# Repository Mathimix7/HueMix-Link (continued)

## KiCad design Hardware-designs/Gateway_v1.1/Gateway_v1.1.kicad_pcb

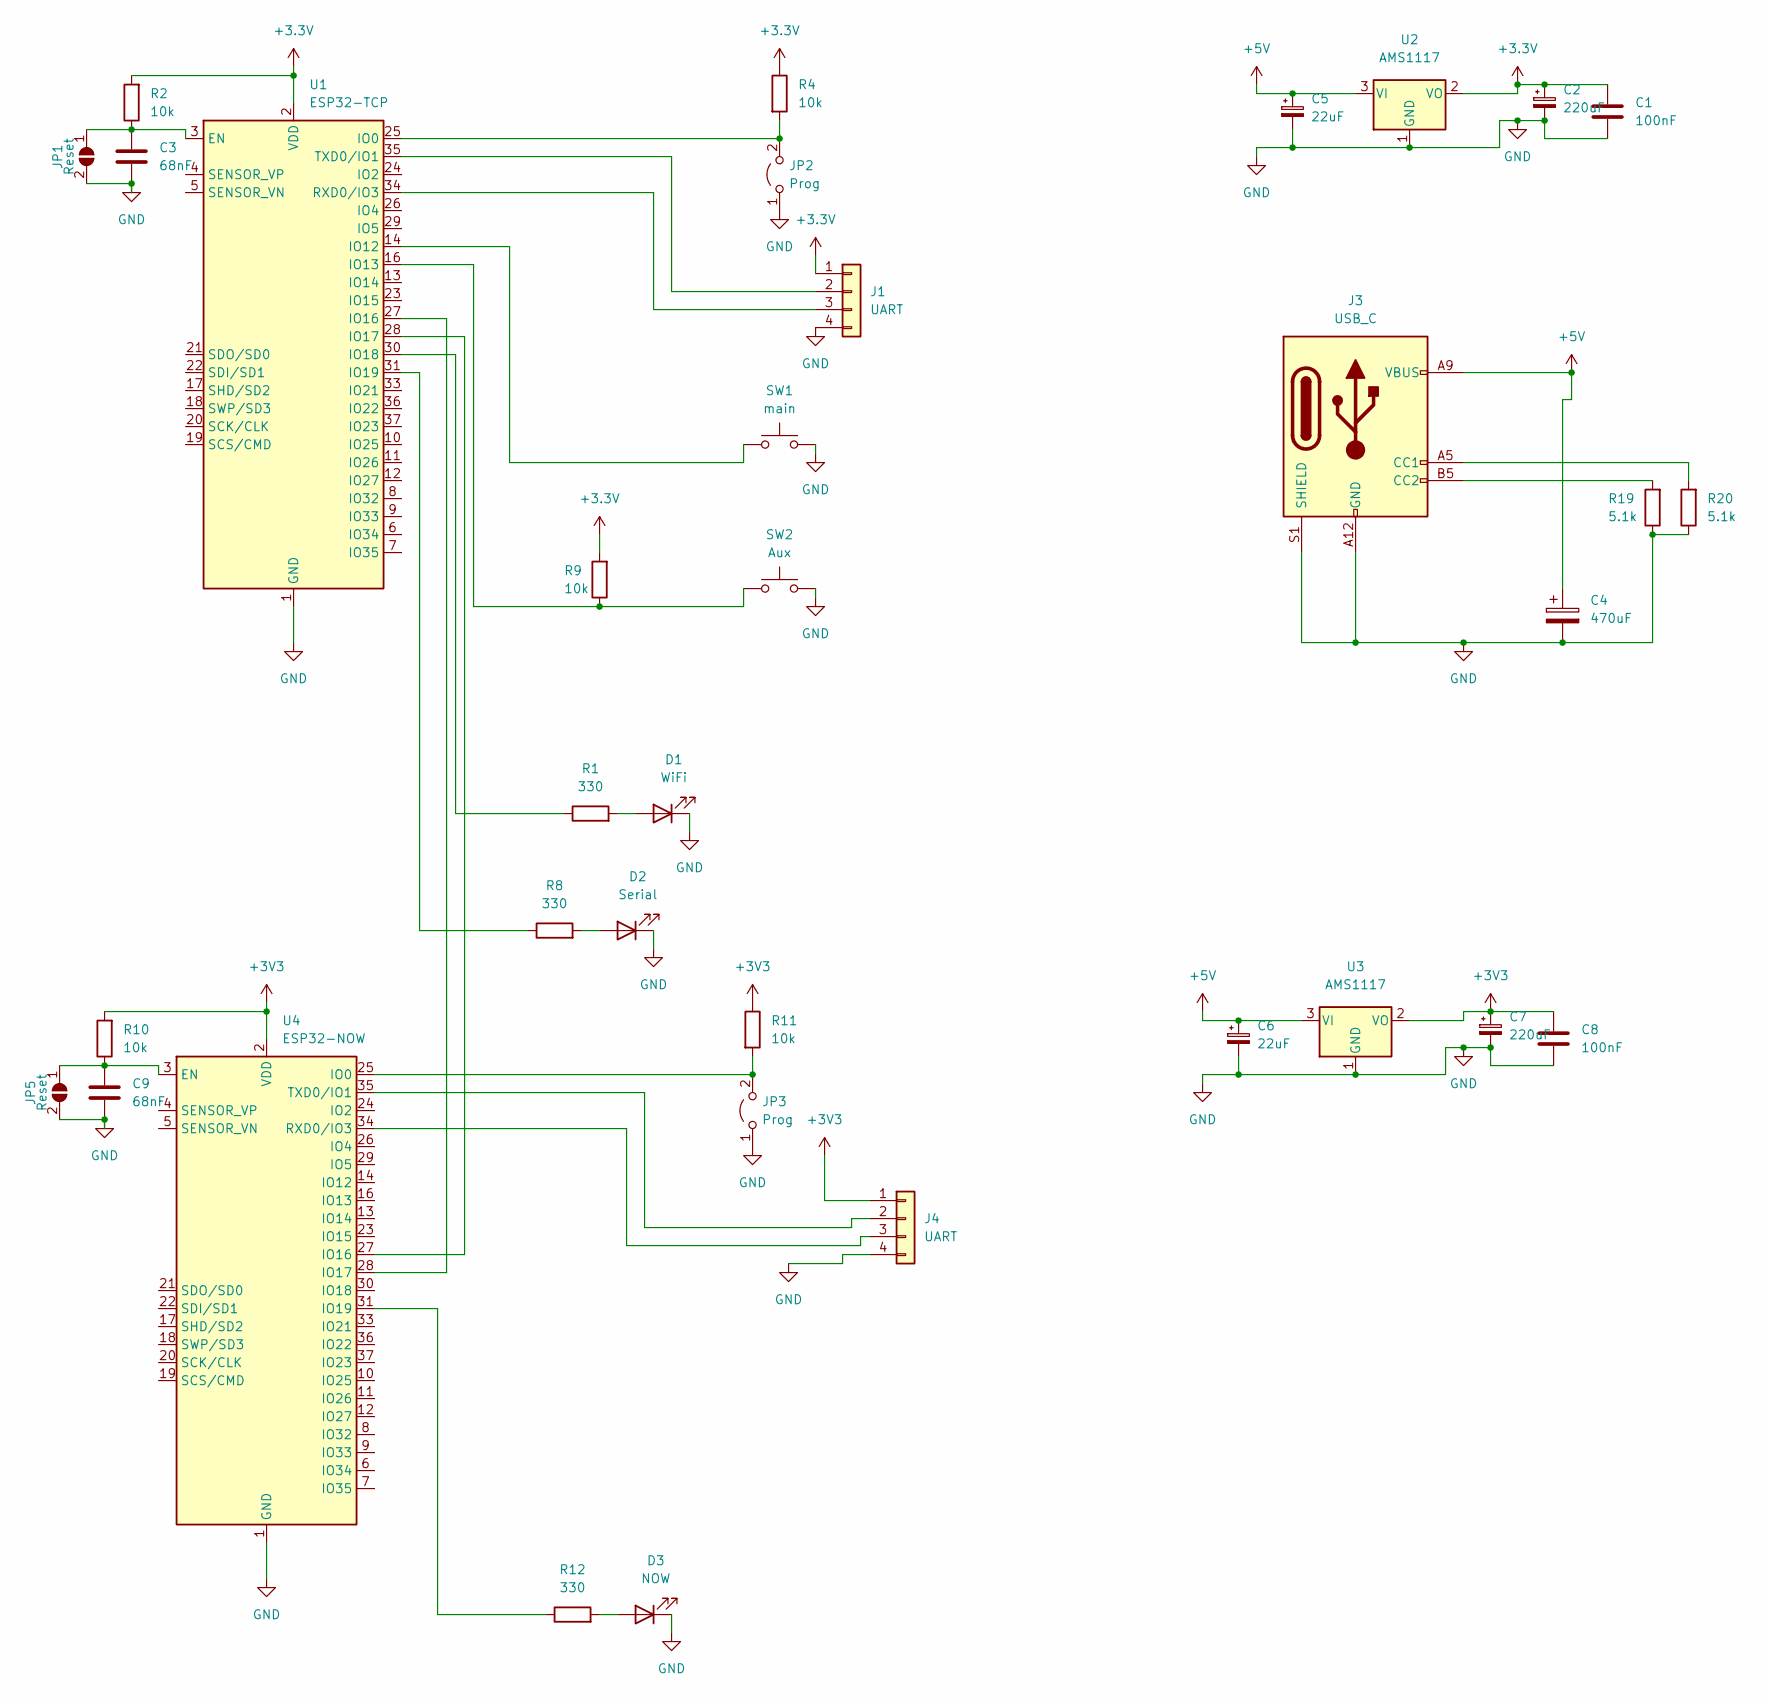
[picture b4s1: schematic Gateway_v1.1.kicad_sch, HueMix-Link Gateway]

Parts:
C1, C8: 100nF; C_0805_2012Metric_Pad1.18x1.45mm_HandSolder
C2, C7: 220uF; CP_EIA-6032-15_Kemet-U_HandSolder
C3, C9: 68nF; C_0805_2012Metric_Pad1.18x1.45mm_HandSolder
C4: 470uF; CP_Radial_D8.0mm_P3.50mm
C5, C6: 22uF; CP_EIA-6032-15_Kemet-U_HandSolder
D1: WiFi; LED_D3.0mm
D2: Serial; LED_D3.0mm
D3: NOW; LED_D3.0mm
J1, J4: UART; PinHeader_1x04_P2.54mm_Vertical
J3: USB_C; USB_C_Receptacle_GCT_USB4125-xx-x-0190_6P_TopMnt_Horizontal
JP1, JP5: Reset; SolderJumper-2_P1.3mm_Open_Pad1.0x1.5mm
JP2, JP3: Prog; PinHeader_1x02_P2.54mm_Vertical
R1, R8, R12: 330; R_1206_3216Metric_Pad1.30x1.75mm_HandSolder
R2, R4, R9, R10, R11: 10k; R_1206_3216Metric_Pad1.30x1.75mm_HandSolder
R19, R20: 5.1k; R_1206_3216Metric_Pad1.30x1.75mm_HandSolder
SW1: main; SW_PUSH-12mm
SW2: Aux; SW_PUSH_6mm
U1: ESP32-TCP; ESP32-WROOM-32
U2, U3: AMS1117; SOT-223-3_TabPin2
U4: ESP32-NOW; ESP32-WROOM-32

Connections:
+3.3V: C1.1, C2.1, J1.1, R2.2, R4.1, R9.2, U1.2 (VDD), U2.2 (VO)
+3V3: C7.1, C8.1, J4.1, R10.2, R11.1, U3.2 (VO), U4.2 (VDD)
+5V: C4.1, C5.1, C6.1, J3.A9 (VBUS), J3.B9 (VBUS), U2.3 (VI), U3.3 (VI)
GND: C1.2, C2.2, C3.2, C4.2, C5.2, C6.2, C7.2, C8.2, C9.2, D1.1 (K), D2.1 (K), D3.1 (K), J1.4, J3.A12 (GND), J3.B12 (GND), J3.S1 (SHIELD), J4.4, JP1.2 (B), JP2.1 (A), JP3.1 (A), JP5.2 (B), R19.1, R20.1, SW1.2, SW2.2, U1.1 (GND), U1.15 (GND), U1.38 (GND), U1.39 (GND), U2.1 (GND), U3.1 (GND), U4.1 (GND), U4.15 (GND), U4.38 (GND), U4.39 (GND)
unnamed: D1.2 (A), R1.2
unnamed: D2.2 (A), R8.2
unnamed: D3.2 (A), R12.2
unnamed: J1.2, U1.35 (TXD0/IO1)
unnamed: J1.3, U1.34 (RXD0/IO3)
unnamed: J3.A5 (CC1), R20.2
unnamed: J3.B5 (CC2), R19.2
unnamed: J4.2, U4.35 (TXD0/IO1)
unnamed: J4.3, U4.34 (RXD0/IO3)
unnamed: C3.1, JP1.1 (A), R2.1, U1.3 (EN)
unnamed: JP2.2 (B), R4.2, U1.25 (IO0)
unnamed: JP3.2 (B), R11.2, U4.25 (IO0)
unnamed: C9.1, JP5.1 (A), R10.1, U4.3 (EN)
unnamed: SW1.1, U1.14 (IO12)
unnamed: R9.1, SW2.1, U1.16 (IO13)
unnamed: U1.27 (IO16), U4.28 (IO17)
unnamed: U1.28 (IO17), U4.27 (IO16)
unnamed: R1.1, U1.30 (IO18)
unnamed: R8.1, U1.31 (IO19)
unnamed: R12.1, U4.31 (IO19)

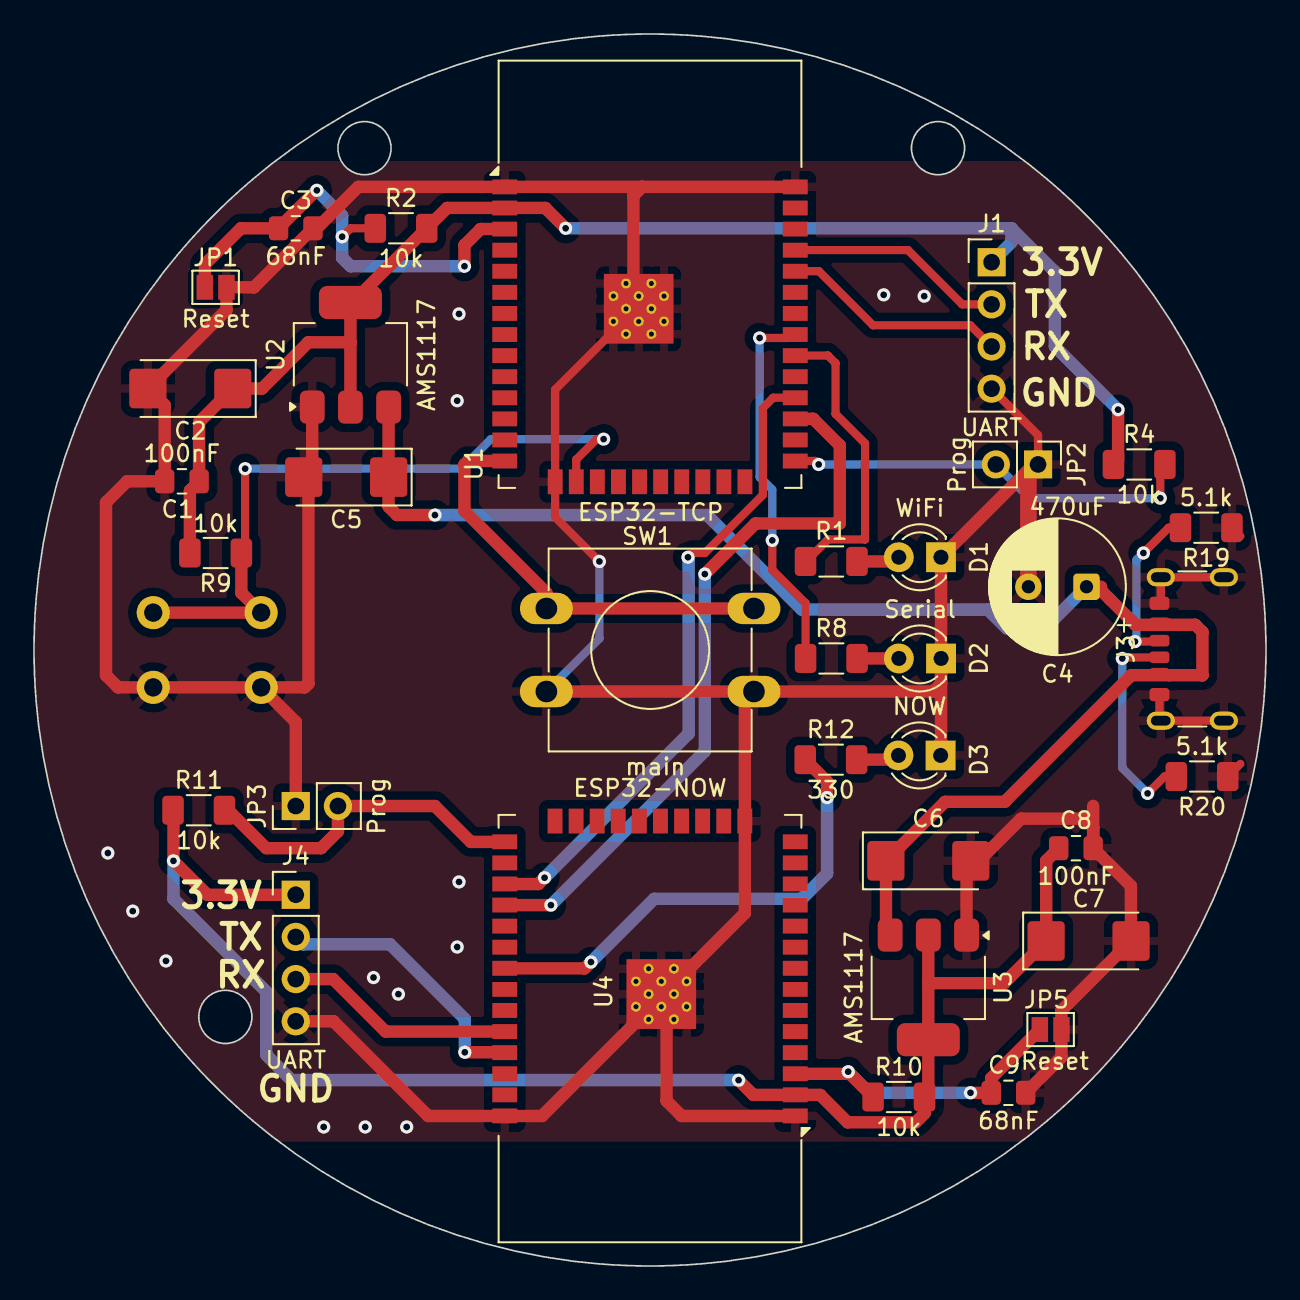
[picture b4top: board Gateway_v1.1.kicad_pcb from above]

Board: 2 copper layers, 74.2 x 74.2 mm, 35 parts (1 on the bottom side), 24 nets.

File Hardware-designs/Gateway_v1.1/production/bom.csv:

Designator,Footprint,Quantity,Value,LCSC Part #
"C1, C8",0805,2,100nF,
"C2, C7",CP_EIA-6032-15_Kemet-U_HandSolder,2,220uF,
"C3, C9",0805,2,1nF,
C4,CP_Radial_D8.0mm_P3.50mm,1,470uF,
"C5, C6",CP_EIA-6032-15_Kemet-U_HandSolder,2,22uF,
D1,LED_D3.0mm,1,WiFi,
D2,LED_D3.0mm,1,Serial,
D3,LED_D3.0mm,1,NOW,
"J1, J4",PinHeader_1x04_P2.54mm_Vertical,2,UART,
J3,USB_C_Receptacle_GCT_USB4125-xx-x-0190_6P_TopMnt_Horizontal,1,USB_C,
"JP1, JP5",SolderJumper-2_P1.3mm_Open_Pad1.0x1.5mm,2,Reset,
"JP2, JP3",PinHeader_1x02_P2.54mm_Vertical,2,Prog,
"R1, R12, R8",1206,3,330,
"R10, R11, R2, R4, R9",1206,5,10k,
"R19, R20",1206,2,5.1k,
SW1,SW_PUSH-12mm,1,main,
SW2,SW_PUSH_6mm,1,Aux,
U1,ESP32-WROOM-32,1,ESP32-TCP,
"U2, U3",SOT-223-3_TabPin2,2,AMS1117,
U4,ESP32-WROOM-32,1,ESP32-NOW,

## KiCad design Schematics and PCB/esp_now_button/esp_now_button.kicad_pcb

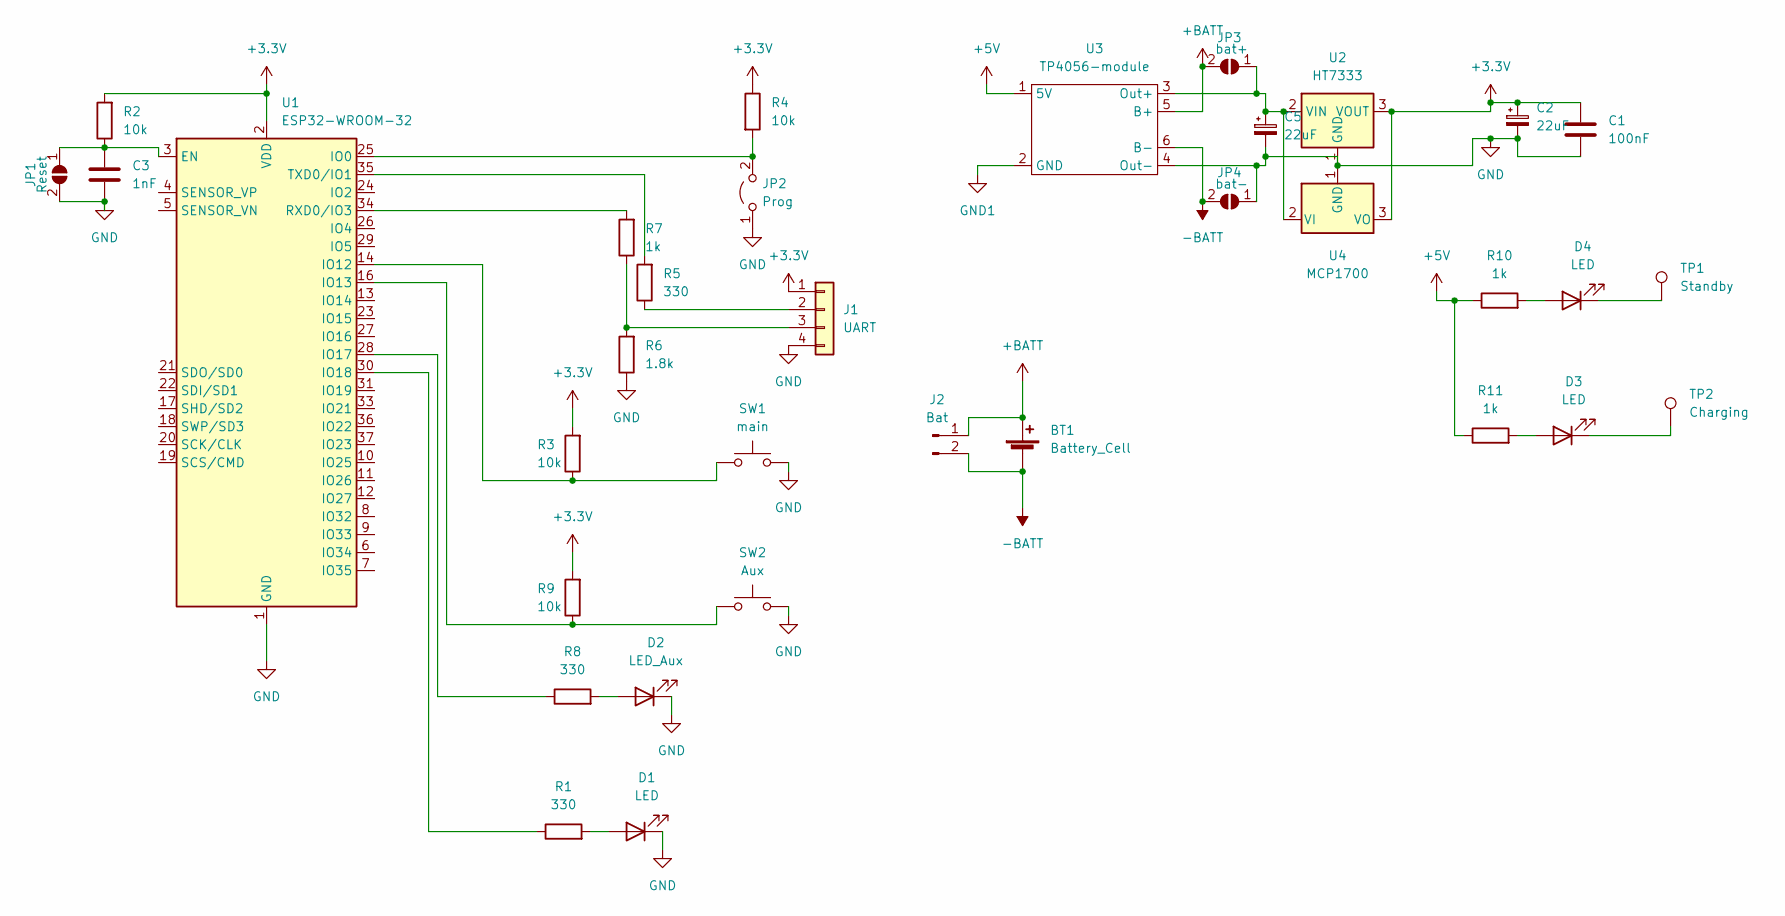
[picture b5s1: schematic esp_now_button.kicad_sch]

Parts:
BT1: Battery_Cell; BatteryHolder_ComfortableElectronic_CH273-2450_1x2450
C1: 100nF; C_0805_2012Metric_Pad1.18x1.45mm_HandSolder
C2, C5: 22uF; CP_EIA-6032-20_AVX-F_Pad2.25x2.35mm_HandSolder
C3: 1nF; C_0805_2012Metric_Pad1.18x1.45mm_HandSolder
D1, D3, D4: LED; LED_D3.0mm
D2: LED_Aux; LED_D3.0mm
J1: UART; PinHeader_1x04_P2.54mm_Vertical
J2: Bat; JST_EH_B2B-EH-A_1x02_P2.50mm_Vertical
JP1: Reset; SolderJumper-2_P1.3mm_Open_Pad1.0x1.5mm
JP2: Prog; PinHeader_1x02_P2.54mm_Vertical
JP3: bat+; SolderJumper-2_P1.3mm_Open_Pad1.0x1.5mm
JP4: bat-; SolderJumper-2_P1.3mm_Open_Pad1.0x1.5mm
R1, R5, R8: 330; R_1206_3216Metric_Pad1.30x1.75mm_HandSolder
R2, R3, R4, R9: 10k; R_1206_3216Metric_Pad1.30x1.75mm_HandSolder
R6: 1.8k; R_1206_3216Metric_Pad1.30x1.75mm_HandSolder
R7, R10, R11: 1k; R_1206_3216Metric_Pad1.30x1.75mm_HandSolder
SW1: main; SW_PUSH-12mm
SW2: Aux; SW_PUSH_6mm
TP1: Standby; TestPoint_THTPad_D1.5mm_Drill0.7mm
TP2: Charging; TestPoint_THTPad_D1.5mm_Drill0.7mm
U1: ESP32-WROOM-32
U2: HT7333; SOT-89-3
U3: TP4056-module; TP4056-18650
U4: MCP1700; TO-92_Inline

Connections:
+3.3V: C1.1, C2.1, J1.1, R2.2, R3.2, R4.1, R9.2, U1.2 (VDD), U2.3 (VOUT), U4.3 (VO)
+5V: R10.1, R11.1, U3.1 (5V)
+BATT: BT1.1 (+), J2.1, JP3.2 (B), U3.5 (B+)
-BATT: BT1.2 (-), J2.2, JP4.2 (B), U3.6 (B-)
GND: C1.2, C2.2, C3.2, C5.2, D1.1 (K), D2.1 (K), J1.4, JP1.2 (B), JP2.1 (A), JP4.1 (A), R6.1, SW1.2, SW2.2, U1.1 (GND), U1.15 (GND), U1.38 (GND), U1.39 (GND), U2.1 (GND), U3.4 (Out-), U4.1 (GND)
GND1: U3.2 (GND)
unnamed: C3.1, JP1.1 (A), R2.1, U1.3 (EN)
unnamed: C5.1, JP3.1 (A), U2.2 (VIN), U3.3 (Out+), U4.2 (VI)
unnamed: D1.2 (A), R1.2
unnamed: D2.2 (A), R8.2
unnamed: D3.1 (K), TP2.1
unnamed: D3.2 (A), R11.2
unnamed: D4.1 (K), TP1.1
unnamed: D4.2 (A), R10.2
unnamed: J1.2, R5.1
unnamed: J1.3, R6.2, R7.1
unnamed: JP2.2 (B), R4.2, U1.25 (IO0)
unnamed: R1.1, U1.30 (IO18)
unnamed: R3.1, SW1.1, U1.14 (IO12)
unnamed: R5.2, U1.35 (TXD0/IO1)
unnamed: R7.2, U1.34 (RXD0/IO3)
unnamed: R8.1, U1.28 (IO17)
unnamed: R9.1, SW2.1, U1.16 (IO13)

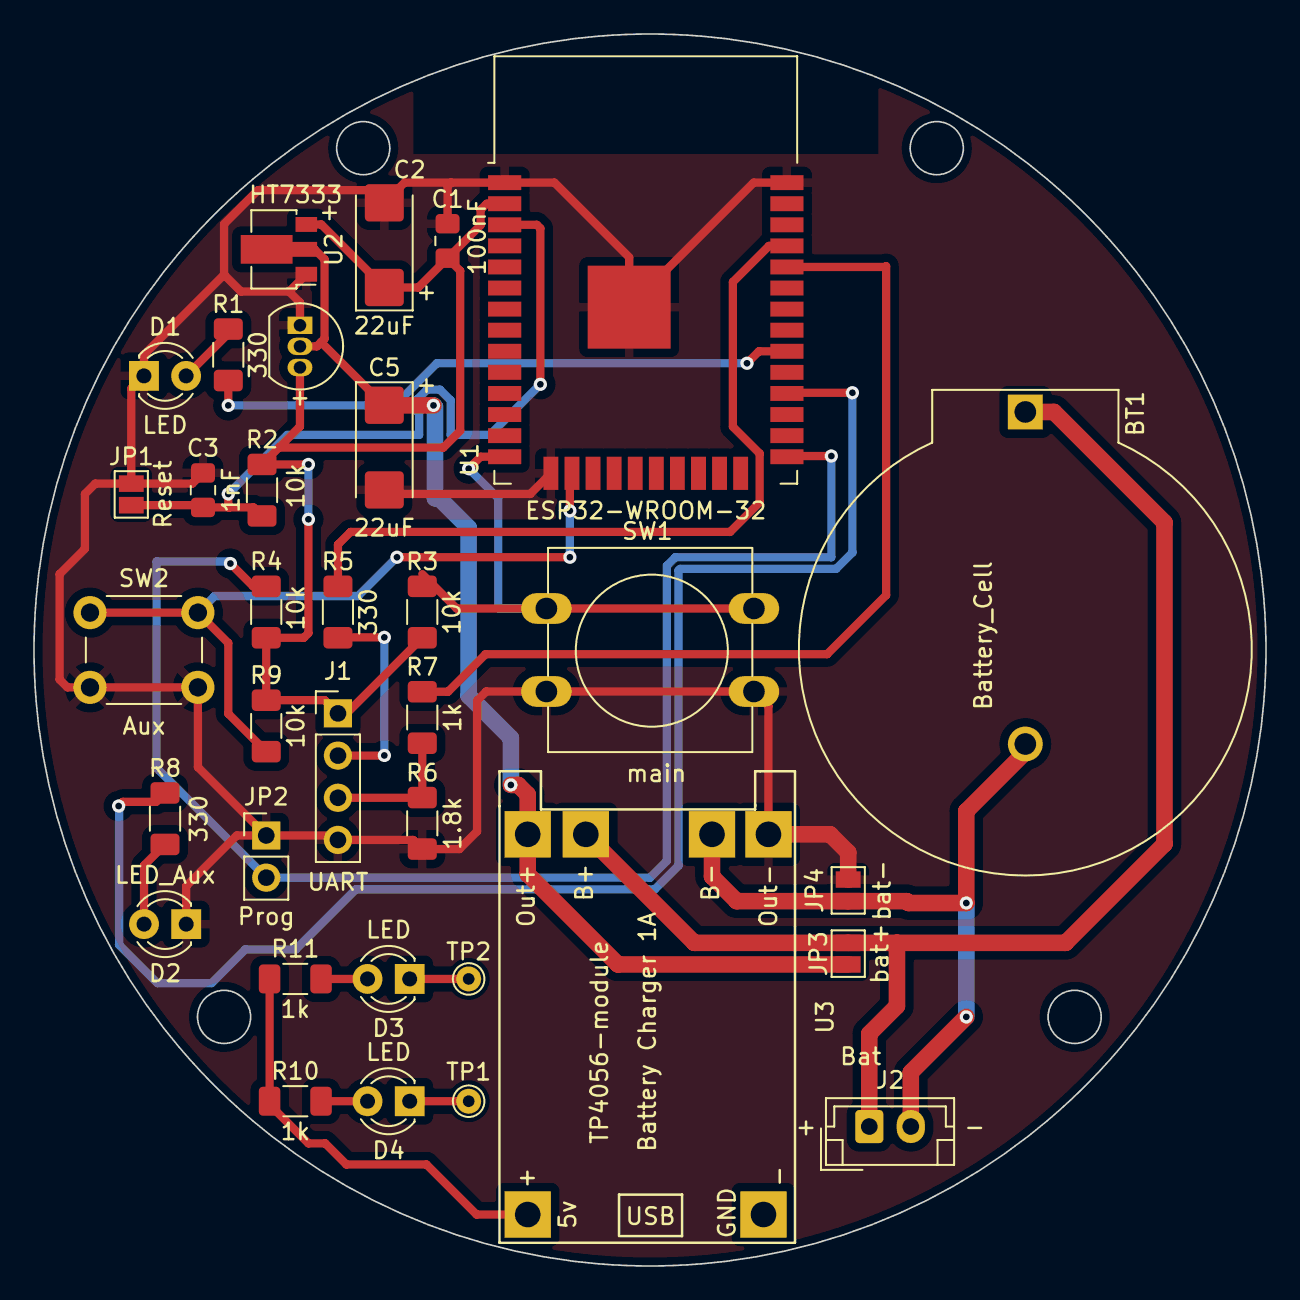
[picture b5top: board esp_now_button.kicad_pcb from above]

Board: 2 copper layers, 74.2 x 74.2 mm, 34 parts (0 on the bottom side), 22 nets.

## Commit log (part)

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2023-06-20 Moved Python files
2023-06-20 add arduino code
2023-06-20 add schematics and pcb
    Kicad files + gerbers
2023-06-20 Add PDF schematics
2023-06-20 add pcb images
2023-06-21 add services linux
2023-06-22 button version for esp8266
    It does not include deep sleep
2023-06-22 Erase data from files
2023-06-22 Update default port value
2023-06-23 Fix holding button and brightness
2023-06-26 Fix arduino files in folders
2023-06-26 tcp_client_server for esp8266
2023-06-26 update macAddress updater with button
2023-06-30 Change pins to pcb
2023-06-30 fix invalid servers macs + socket timeout
2023-06-30 change timeout to recieve
2023-07-01 fix holding sending wrong data
2023-07-01 update name
2023-07-03 update website main screen and buttons
    New color, responsive, better alerts, cancel buttons
2023-07-03 add ico
2023-07-03 changed servers and settings to new website style
2023-07-03 remove prints
2023-07-03 add new ico logo
2023-07-03 remove debug
2023-07-03 fix styles
2023-07-03 Fix enter action
    (Addition to website improvement pull request)
2023-07-08 add led off option
2023-07-09 new server information
    Server information, led off times, firmware update through website
2023-07-10 add loading screen and timeout for servers data
2023-07-10 fix erros loading
2023-07-10 fetch time from tcp instead of api
2023-07-10 bug fix
2023-07-10 Rename to setupRename.html
2023-09-02 duplicated files
2023-09-05 Create website blueprints
2023-09-05 Create API for buttons
2023-11-18 add server api support
2024-01-27 Create LICENSE
2025-12-07 Add .gitignore and update platformio.ini; refactor button handling in gateway_net_node and normal_button
2025-12-11 Refactor color handling and enhance light state management
    - Updated color conversion methods in ColorController to utilize model_id for gamut selection.
    - Added model_id to light state updates in HueStateManager.
    - Enhanced API responses to include model_id for lights.
    - Improved rooms overview data retrieval to use model_id for color conversions.
2025-12-12 WIP: local changes
2025-12-27 Final esp firmware version
2025-12-27 New network service, website endpoints, and configuration
2025-12-27 Final html version
2025-12-27 edit gitignore
2025-12-27 Fix backup reload, add notifiers, and file not existing management
2025-12-27 Add requirements.txt
2025-12-27 Add license and readme
2025-12-27 add waitress wsgi support
2025-12-27 Refactor logging levels to debug for specific events and add logging service for improved log management
2025-12-27 add logo
2025-12-27 Rename HueMix
2025-12-27 Add hostname option
2025-12-27 Update version
2025-12-27 Make installer output more readable with colored markers
2025-12-27 Enhance usage output with color-coded options for better readability
2025-12-27 Update usage output colors for improved visibility
2025-12-27 Update usage output colors for improved readability
2025-12-27 Remove symbols
2025-12-27 Fix hosts local installation
2025-12-27 Fix logging messages format for systemd
2025-12-27 Remove upload_port entries from platformio.ini for all environments
2025-12-27 WIP: Proxy setup
2025-12-27 Finish proxy for webserver and new domain management. Remove flask port setup
2025-12-27 Finish touches for install script.
2025-12-27 Make commands silent
2025-12-27 Fix service_update_finish
2025-12-27 Fix permission setup
2025-12-27 Fix local domain errors
2025-12-27 Use HAProxy
2025-12-27 fixe old hostname changes with avahi service file
2025-12-27 Fix hostname with .local
2025-12-27 Add automation engine system status
2025-12-27 Upgrade version
2025-12-28 Change led type
2025-12-28 Refactor LED control logic to use LED_ACTIVE_HIGH for consistency
2025-12-29 Add clear LED schedule functionality with confirmation modal
2025-12-29 Remove configured scene from button when original scene is deleted. And handle delete/add SSE events for lights, scenes, and rooms
2025-12-29 Fix: Replace print with logger
2025-12-29 Change devices ids to uuid4
2025-12-30 Fix lights brightness issue not restoring properly
2025-12-30 Remove print
2025-12-30 Fix issue with not configured buttons
2025-12-30 Improved all bridge overview information to update in real time and
2025-12-30 Flash button when pressed on settings page
2025-12-30 Version bump
2025-12-30 Made local flag opposite
2025-12-30 Add backup deletion
2025-12-30 Fix issue with service not being detected properly
2026-01-13 Add device type definitions and update packet payloads for gateway, light, and button. Fix button not activating with short presses
2026-01-13 feat: Add remote control support and configuration
    - Updated DeviceManager to handle remote devices with new device_type parameter.
    - Enhanced NetworkServer to process HELLO packets from remote controls and manage pairing.
    - Implemented PacketDecoder changes to recognize remote devices and their actions.
    - Modified PairingManager to include remote devices in allowed types.
    - Added API endpoints for configuring remote controls with per-button actions and room mappings.
    - Created a new modal in the frontend for remote configuration, allowing users to set actions and scenes for each button.
2026-01-13 Implementation of battery status
2026-01-13 bump
2026-01-13 Fix installer logs
2026-01-13 Add remote to pairing devices
2026-01-13 Fix direction toggle on remote
2026-01-13 Improve HAProxy restart command to suppress unnecessary output
2026-01-15 Fix resistor divider
2026-01-25 OTA update working for all devices
2026-01-26 Change signature protocol to always include full length, fix radio node not updating properly.
2026-01-27 Add build_release script, update platformio.ini, and enhance OTA functionality
2026-01-27 Add serial firmware upload
2026-01-28 Add scene cycle action for remote buttons and enhance device management UI
2026-01-31 Refactor color conversion methods and enhance network server reliability with socket checks
2026-01-31 Fix small ota issues
2026-02-01 Refactor OTA HTML to use local ESPTool bundle instead of unpkg
2026-02-01 version
2026-02-01 Bump version to 3.8.1; update DOUBLE_TAP_WINDOW to 1000ms in button firmware and improve remote button event handling
2026-02-12 Update pairing to https for bridge pro
2026-02-12 Update pairing to https fix
2026-02-13 Hardware Design
2026-02-14 Update color functions and add new lightstrip model
2026-02-16 Motion sensor initial commit
2026-02-17 Restore images
2026-02-17 Remove DS_Store
2026-02-17 Ignore KiCad backup/local files in Hardware-designs
2026-02-18 Add pcb images, step file, and pdf schematic for all hardware designs.
2026-02-18 Add production output for remote.
2026-02-18 Revert "Update color functions and add new lightstrip model"
    This reverts commit 1c41b5c88474862ff84bd28d54ce498e215f0f58.
2026-02-20 add motion sensor hardware
2026-02-21 Add serial labels on pcb
2026-02-22 feat: Configurable 1-4 button remotes with triple-tap configuration
    Add flexible button count (1-4) for ESP32 remotes configured via
    triple-tap reset + held button combinations. Includes hardware pattern
    validation, dynamic wakeup masks, custom UI naming (Circle/Center/Square),
    context-aware defaults, and immediate auto-registration support.
    Remotes can now operate as 1, 2, 3, or 4-button devices with proper
    firmware/UI adaptation. Backward compatible with existing remotes.
2026-02-22 Bump version
2026-02-23 Add Ota Support for motion sensors and add cooldown command.
2026-02-23 change to debug logs
2026-02-24 Bump motion sensor version
2026-02-24 Revert "Revert "Update color functions and add new lightstrip model""
    This reverts commit 3ccff76ec2a8d7b2dcd7205871dbaeb94320e082.
2026-02-24 Fix import issue
2026-02-24 Fix import error
2026-02-24 Refactor lightstrip configurations and update OTA management for improved device handling
2026-02-24 Remove lightstrip_model5.cpp file, consolidating firmware for models 5 and 6 into a single codebase.
2026-02-24 Improve gateway led status,
2026-02-24 Enhance building script
2026-02-24 Fix button building script name
2026-02-24 Fix motion sensor ota failure init
2026-02-24 Finish ota updates for motion sensor.
2026-02-24 Remove old online status
2026-02-24 Lower PWM frequency to stabilize signal
2026-02-25 Add update restrictions for net node and check for Web Serial API availability
2026-02-25 Bump version to 3.10.2
2026-02-25 Add bootloader and particions on serial first boot.
2026-02-25 Add reset
2026-02-25 Fix small issues with installer and bridge controller when loading from backup
2026-02-25 Made default http port 80, added https for web serial api support.
2026-02-25 Serial API availability with HTTPS redirection prompt.
2026-02-25 make https to argument opposite on install script
2026-02-25 Improve empty state messages in templates
2026-03-01 correction voltage regulator
2026-03-09 Add hue_config_sync service and integrate with scene/room deletion handling
2026-03-10 Ensure new rooms are synced with info.
2026-03-10 Add motion sensor endpoints on pairing page.
2026-03-12 Ignore auto saved files
2026-03-12 Magnetic Sensor
2026-03-12 Add readme
2026-03-18 Use last seen gateway instead of first gateway for remotes and buttons.
2026-03-18 Fix ota chunks to also use best gateway for remotes and buttons
2026-03-18 Update motion sensor reset button to work more efficiently.
2026-03-18 Add motion as option for long range pairing.
2026-03-28 Start esp firmware for door sensor
2026-03-28 feat: Add USB Serial Gateway support
    - Updated requirements to include pyserial for serial communication.
    - Implemented API endpoints for managing serial gateway settings and retrieving available serial ports.
    - Enhanced admin interface to configure USB serial gateway settings, including enabling/disabling, selecting ports, and setting baud rates.
    - Introduced SerialGatewayTransport class to handle serial communication, including packet framing and handshake.
    - Updated gateway management to support serial gateways, including identification and handling during deletion.
    - Modified frontend templates to display serial gateway information and settings.
2026-03-29 Finish implementation for door sensors
2026-03-29 Fix room state retrieval and enhance SSE handling for room updates
2026-03-29 Magnetic sensor update
2026-03-29 Fix door sensor not turning off due to light threshold.
2026-03-29 Add door closing timer
2026-03-30 Finish serial python radio node
2026-04-01 finish serial support
2026-04-02 update readme with new devices
2026-04-02 Fix mesh page to ping gateways
2026-04-02 Add wifi state for gateway python based on ip
2026-04-02 Make sensor after time second based
2026-04-03 Minor KiCad files update for all devices
2026-04-03 Add 3D Models
2026-04-03 Disable unused 3d models
2026-04-03 Add images to readme
2026-04-03 update radio node
2026-04-04 Organized html into css and js files
2026-04-04 Refactor tooltip positioning logic for improved responsiveness
2026-04-04 Update auto-refresh interval from 3 seconds to 2 seconds
2026-04-04 Fix bug dimming breaking at 0%
2026-04-04 Add table of contents and dashboard images
2026-04-04 Update repo to public
2026-04-04 Lightstrip version 2
2026-04-05 Fix motion sensors canceling due to SSE delays.
2026-04-25 Increase esp8266 acknowledgment timeout
2026-04-25 Fix state mismatch on sse
2026-04-25 Increase timeout
2026-04-25 Add system metrics
2026-04-26 Fix magnetic sensor pcb
2026-06-08 feat: Add plugin management and battery calculation features
    - Introduced a new PluginManager for managing optional plugins, including installation, lifecycle management, and event handling.
    - Added PluginInstallService to handle plugin installation sessions and progress tracking.
    - Implemented battery percentage calculation logic in a new battery.py service, supporting different battery types.
    - Enhanced OTA management by adding preferred gateway MAC address in OTASession.
    - Updated pairing.html to include an option for "Plugin Devices Only" in the device selection dropdown.
    - Created a new battery service to provide shared battery helpers across device views and services.
2026-06-09 Add plugins to gitignore
2026-06-09 Add service restart privileges from app
